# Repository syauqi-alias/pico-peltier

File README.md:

# pico-peltier
A TEC Controller using Pico RP2350 with Analog Devices LT8722 full bridge driver rated at 15V 4A

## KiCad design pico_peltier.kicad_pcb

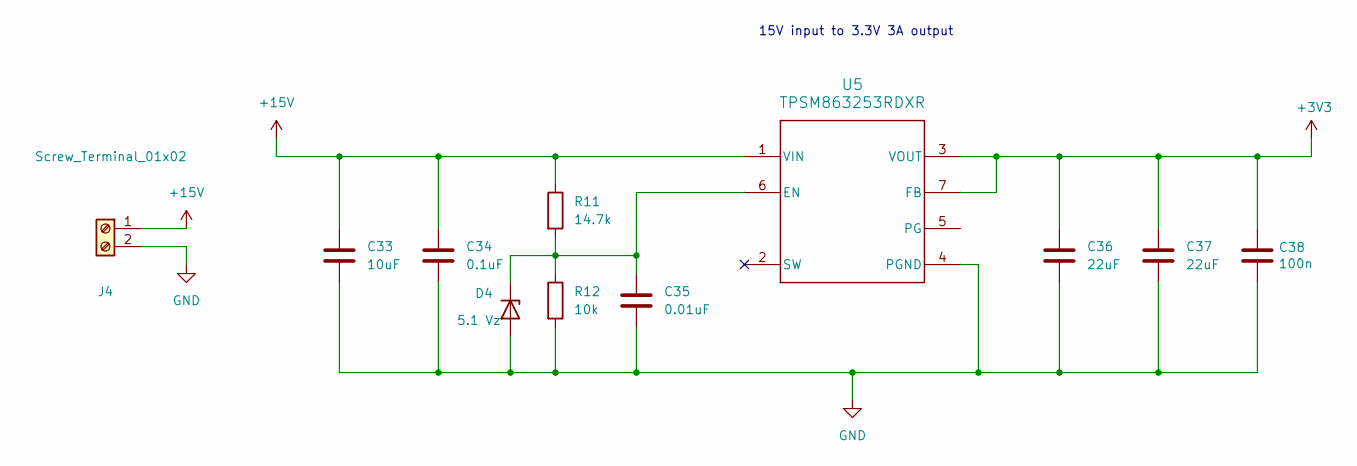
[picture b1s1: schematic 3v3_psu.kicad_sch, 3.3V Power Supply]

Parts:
C33: 10uF; C_0805_2012Metric_Pad1.18x1.45mm_HandSolder; mouser 187-CL21A106KAYNNNE
C34: 0.1uF; C_0805_2012Metric_Pad1.18x1.45mm_HandSolder; mouser 581-08053D104KAT2A
C35: 0.01uF; C_0805_2012Metric_Pad1.18x1.45mm_HandSolder; mouser KGM21NR71E103KT
C36, C37: 22uF; C_0603_1608Metric_Pad1.08x0.95mm_HandSolder; mouser 581-KAM15CT70J226KT
C38: 100n; C_0603_1608Metric_Pad1.08x0.95mm_HandSolder; mouser 581-KGM15AR70J104KM
D4: 5.1 Vz; D_SOD-123; mouser 621-MMSZ5231B-F
J4: Screw_Terminal_01x02; Altech_AK100_1x02_P5.00mm; mouser 845-30.002
R11: 14.7k; R_0603_1608Metric_Pad0.98x0.95mm_HandSolder; mouser 603-RC0603FR-1014K7L
R12: 10k; R_0603_1608Metric_Pad0.98x0.95mm_HandSolder; mouser 71-CRCW060310K0FKEE
U5: TPSM863253RDXR; VREG_TPSM863253RDXR; mouser 595-TPSM863253RDXR

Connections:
+3V3: C36.1, C37.1, C38.1, U5.3 (VOUT), U5.7 (FB), U5.14 (VOUT), U5.15 (VOUT), U5.16 (VOUT), U5.17 (VOUT), U5.18 (VOUT), U5.19 (VOUT); also elsewhere on the board
+15V: C33.1, C34.1, J4.1, R11.1, U5.1 (VIN); also elsewhere on the board
GND: C33.2, C34.2, C35.2, C36.2, C37.2, C38.2, D4.2 (A), J4.2, R12.2, U5.4 (PGND); also elsewhere on the board
unnamed: C35.1, D4.1 (K), R11.2, R12.1, U5.6 (EN)

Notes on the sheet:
15V input to 3.3V 3A output

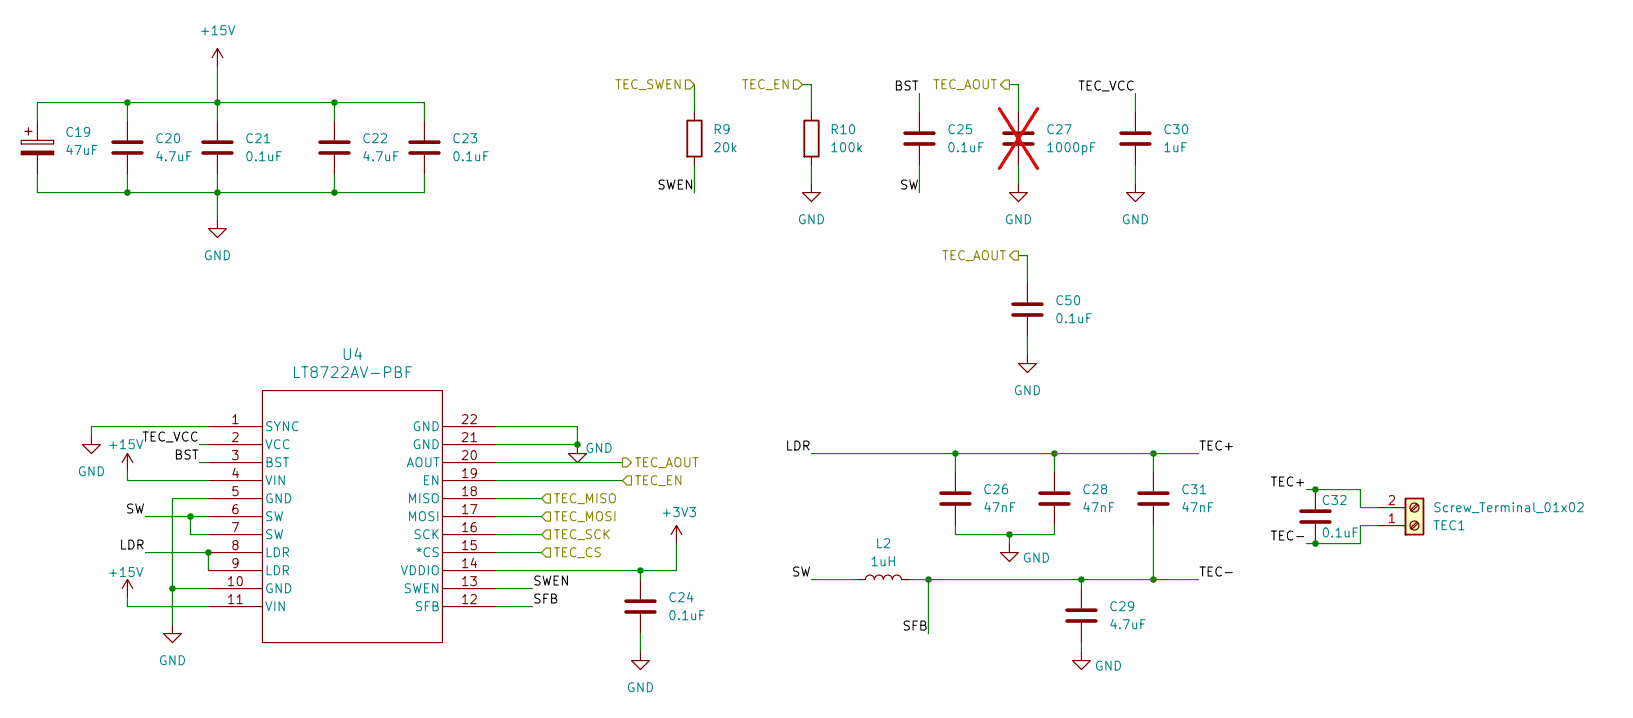
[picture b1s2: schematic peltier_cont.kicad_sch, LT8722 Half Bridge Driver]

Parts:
C19: 47uF; CP_EIA-7343-31_Kemet-D_HandSolder; mouser 581-TAJD476M020R
C20, C22, C29: 4.7uF; C_1206_3216Metric_Pad1.33x1.80mm_HandSolder; mouser 581-12063C475KAT2A
C21, C23, C24, C25, C32, C50: 0.1uF; C_0603_1608Metric_Pad1.08x0.95mm_HandSolder; mouser 187-CL10A104KA8NNNC
C26, C28, C31: 47nF; C_0603_1608Metric_Pad1.08x0.95mm_HandSolder; mouser 81-GCJ188R71E473KA1D
C27: 1000pF; C_0603_1608Metric_Pad1.08x0.95mm_HandSolder; mouser 581-06033C102KAT2A; not fitted
C30: 1uF; C_0603_1608Metric_Pad1.08x0.95mm_HandSolder; mouser 81-GCM188R71E105KA4D
L2: 1uH; L_Coilcraft_XAL4020-XXX; mouser 994-XAL4020-102MEC
R9: 20k; R_0603_1608Metric_Pad0.98x0.95mm_HandSolder; mouser 71-CRCW0603-20K-E3
R10: 100k; R_0603_1608Metric_Pad0.98x0.95mm_HandSolder; mouser 660-SG73P1JTTD1003F
TEC1: Screw_Terminal_01x02; Altech_AK100_1x02_P5.00mm; mouser 845-30.002
U4: LT8722AV-PBF; LQFN18_3X3X0.95_ADI-M; mouser 584-LT8722AVPBF

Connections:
+3V3: C24.1, U4.14 (VDDIO); also elsewhere on the board
+15V: C19.1, C20.1, C21.1, C22.1, C23.1, U4.4 (VIN), U4.11 (VIN); also elsewhere on the board
/mcu_rp2354a/GPIO20: U4.18 (MISO); also elsewhere on the board
/mcu_rp2354a/GPIO21: U4.16 (SCK); also elsewhere on the board
/mcu_rp2354a/GPIO22: U4.15 (*CS); also elsewhere on the board
/mcu_rp2354a/GPIO23: U4.17 (MOSI); also elsewhere on the board
/mcu_rp2354a/GPIO24: R9.1; also elsewhere on the board
/mcu_rp2354a/GPIO25: R10.1, U4.19 (EN); also elsewhere on the board
/mcu_rp2354a/GPIO29_ADC3: C27.1, C50.1, U4.20 (AOUT); also elsewhere on the board
/peltier_cont/BST: C25.1, U4.3 (BST)
/peltier_cont/LDR: C26.1, C28.1, C31.1, C32.1, TEC1.2, U4.8 (LDR), U4.9 (LDR)
/peltier_cont/SFB: C29.1, C31.2, C32.2, L2.2, TEC1.1, U4.12 (SFB)
/peltier_cont/SW: C25.2, L2.1, U4.6 (SW), U4.7 (SW)
/peltier_cont/SWEN: R9.2, U4.13 (SWEN)
/peltier_cont/TEC_VCC: C30.1, U4.2 (VCC)
GND: C19.2, C20.2, C21.2, C22.2, C23.2, C24.2, C26.2, C27.2, C28.2, C29.2, C30.2, C50.2, R10.2, U4.1 (SYNC), U4.5 (GND), U4.10 (GND), U4.21 (GND), U4.22 (GND); also elsewhere on the board

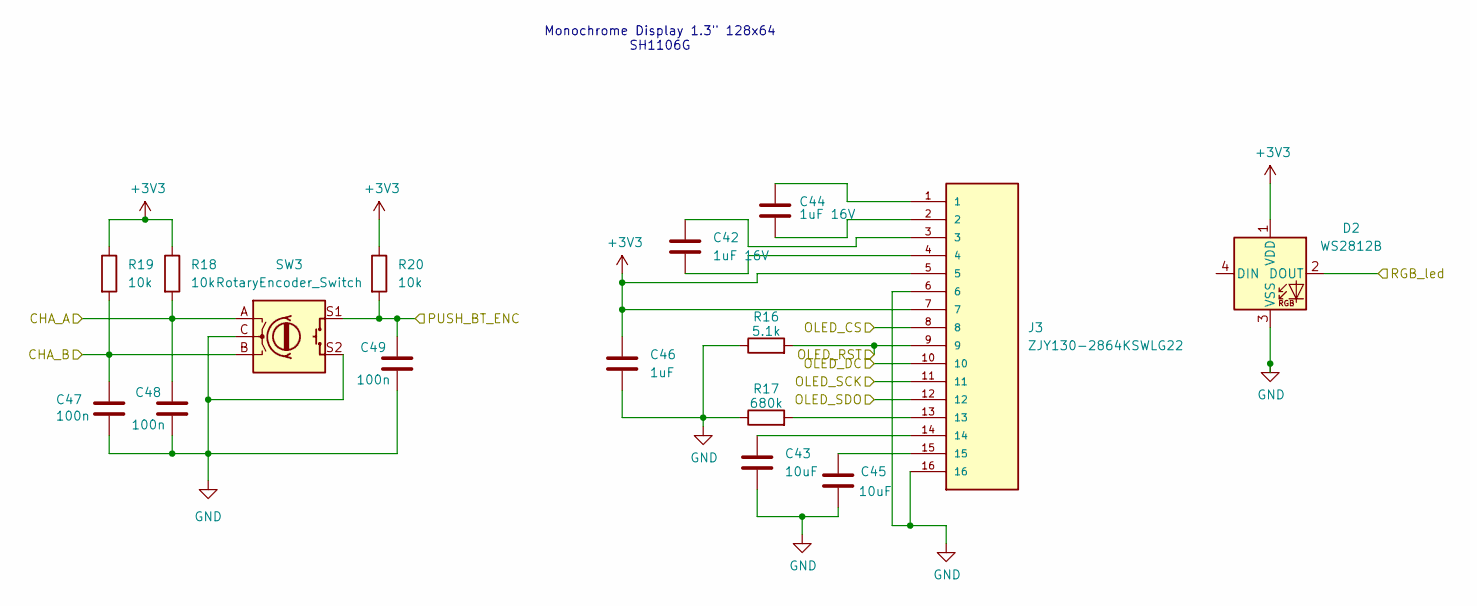
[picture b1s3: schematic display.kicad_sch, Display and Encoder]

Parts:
C42, C44: 1uF 16V; C_0603_1608Metric_Pad1.08x0.95mm_HandSolder; mouser 81-GCM188R71E105KA4D
C43, C45: 10uF; C_0805_2012Metric; mouser 187-CL21A106KAYNNNE
C46: 1uF; C_0603_1608Metric_Pad1.08x0.95mm_HandSolder; mouser 81-GCM188R71E105KA4D
C47, C48, C49: 100n; C_0603_1608Metric_Pad1.08x0.95mm_HandSolder; mouser 581-KGM15AR70J104KM
D2: WS2812B; LED_WS2812B_PLCC4_5.0x5.0mm_P3.2mm; mouser 474-COM-24837
J3: ZJY130-2864KSWLG22; AMPHENOL_F3311A7H121016E200; MPN F3311A7H121016E200; mouser 649-311A7H121016E200
R16: 5.1k; R_0603_1608Metric_Pad0.98x0.95mm_HandSolder; MPN CR0603-FX-5101ELF; mouser 652-CR0603FX-5101ELF
R17: 680k; R_0603_1608Metric_Pad0.98x0.95mm_HandSolder; MPN CRCW0603680KFKEAHP; mouser 71-CRCW0603680KFKEAH
R18, R19, R20: 10k; R_0603_1608Metric_Pad0.98x0.95mm_HandSolder; mouser 71-CRCW060310K0FKEE
SW3: RotaryEncoder_Switch; RotaryEncoder_Bourns_Vertical_PEC12R-3x17F-Sxxxx; mouser 652-PEC12R3220FS0024

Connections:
+3V3: C46.1, D2.1 (VDD), J3.5, J3.7, R18.1, R19.1, R20.1; also elsewhere on the board
/display/CHA_A: C48.1, R18.2, SW3.A; also elsewhere on the board
/display/CHA_B: C47.1, R19.2, SW3.B; also elsewhere on the board
/display/OLED_CS: J3.8; also elsewhere on the board
/display/OLED_DC: J3.10; also elsewhere on the board
/display/OLED_RST: J3.9, R16.2; also elsewhere on the board
/display/OLED_SCK: J3.11; also elsewhere on the board
/display/OLED_SDO: J3.12; also elsewhere on the board
/display/PUSH_BT_ENC: C49.1, R20.2, SW3.S1; also elsewhere on the board
/display/RGB_led: D2.2 (DOUT); also elsewhere on the board
GND: C43.2, C45.2, C46.2, C47.2, C48.2, C49.2, D2.3 (VSS), J3.6, J3.16, R16.1, R17.1, SW3.C, SW3.S2; also elsewhere on the board
unnamed: C42.1, J3.3
unnamed: C42.2, J3.4
unnamed: C43.1, J3.14
unnamed: C44.1, J3.1
unnamed: C44.2, J3.2
unnamed: C45.1, J3.15
unnamed: J3.13, R17.2

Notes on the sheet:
Monochrome Display 1.3" 128x64 SH1106G

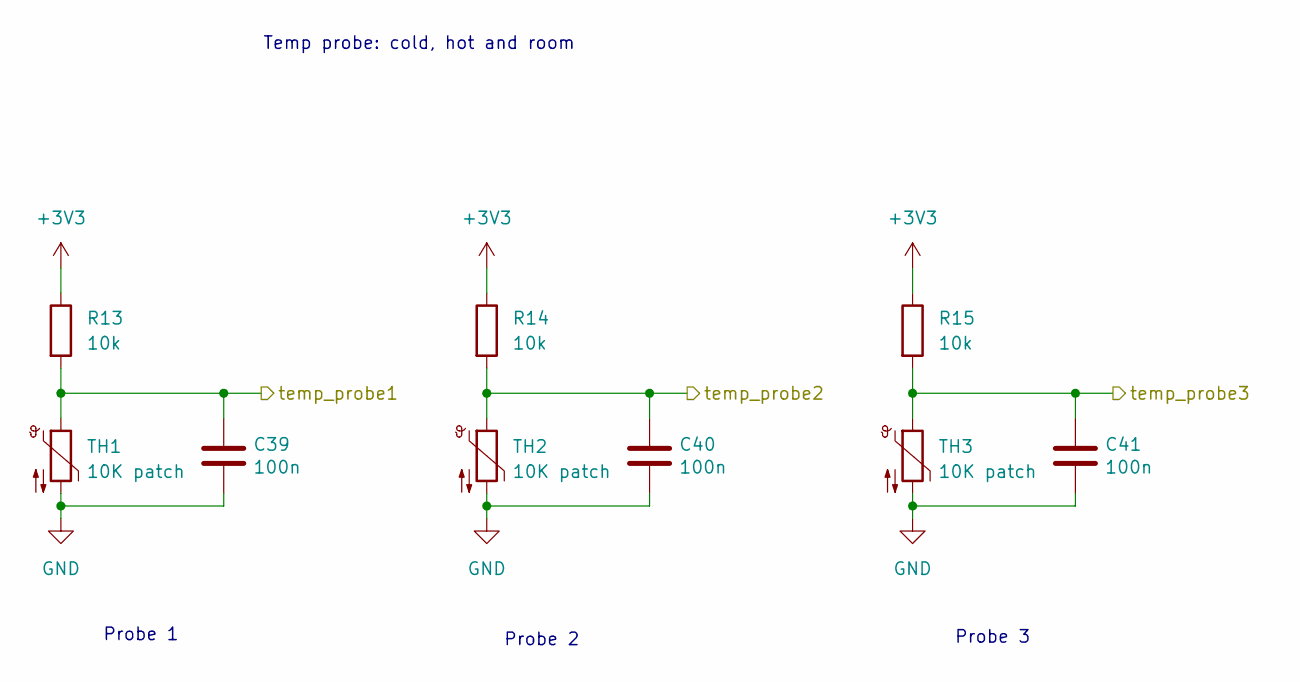
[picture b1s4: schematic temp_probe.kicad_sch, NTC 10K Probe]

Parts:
C39, C40, C41: 100n; C_0603_1608Metric_Pad1.08x0.95mm_HandSolder; mouser 581-KGM15AR70J104KM
R13, R14, R15: 10k; R_0603_1608Metric_Pad0.98x0.95mm_HandSolder; mouser 603-RT0603WRE0710KL
TH1, TH2, TH3: 10K patch; Altech_AK100_1x02_P5.00mm; mouser 845-30.002

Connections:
+3V3: R13.1, R14.1, R15.1; also elsewhere on the board
/mcu_rp2354a/GPIO26_ADC0: C39.1, R13.2, TH1.1; also elsewhere on the board
/mcu_rp2354a/GPIO27_ADC1: C40.1, R14.2, TH2.1; also elsewhere on the board
/mcu_rp2354a/GPIO28_ADC2: C41.1, R15.2, TH3.1; also elsewhere on the board
GND: C39.2, C40.2, C41.2, TH1.2, TH2.2, TH3.2; also elsewhere on the board

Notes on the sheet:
Temp probe: cold, hot and room
Probe 1
Probe 2
Probe 3

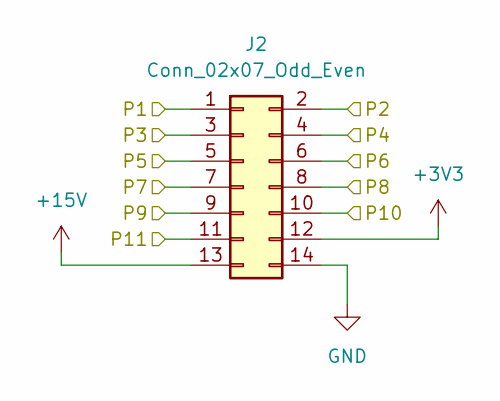
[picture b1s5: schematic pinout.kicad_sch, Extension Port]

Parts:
J2: Conn_02x07_Odd_Even; PinSocket_2x07_P2.54mm_Vertical; mouser 571-5-534236-7

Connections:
+3V3: J2.12; also elsewhere on the board
+15V: J2.13; also elsewhere on the board
/mcu_rp2354a/GPIO0: J2.1; also elsewhere on the board
/mcu_rp2354a/GPIO1: J2.2; also elsewhere on the board
/mcu_rp2354a/GPIO2: J2.3; also elsewhere on the board
/mcu_rp2354a/GPIO12: J2.4; also elsewhere on the board
/mcu_rp2354a/GPIO13: J2.5; also elsewhere on the board
/mcu_rp2354a/GPIO14: J2.6; also elsewhere on the board
/mcu_rp2354a/GPIO15: J2.7; also elsewhere on the board
/mcu_rp2354a/GPIO16: J2.8; also elsewhere on the board
/mcu_rp2354a/GPIO17: J2.9; also elsewhere on the board
/mcu_rp2354a/GPIO18: J2.10; also elsewhere on the board
/mcu_rp2354a/GPIO19: J2.11; also elsewhere on the board
GND: J2.14; also elsewhere on the board

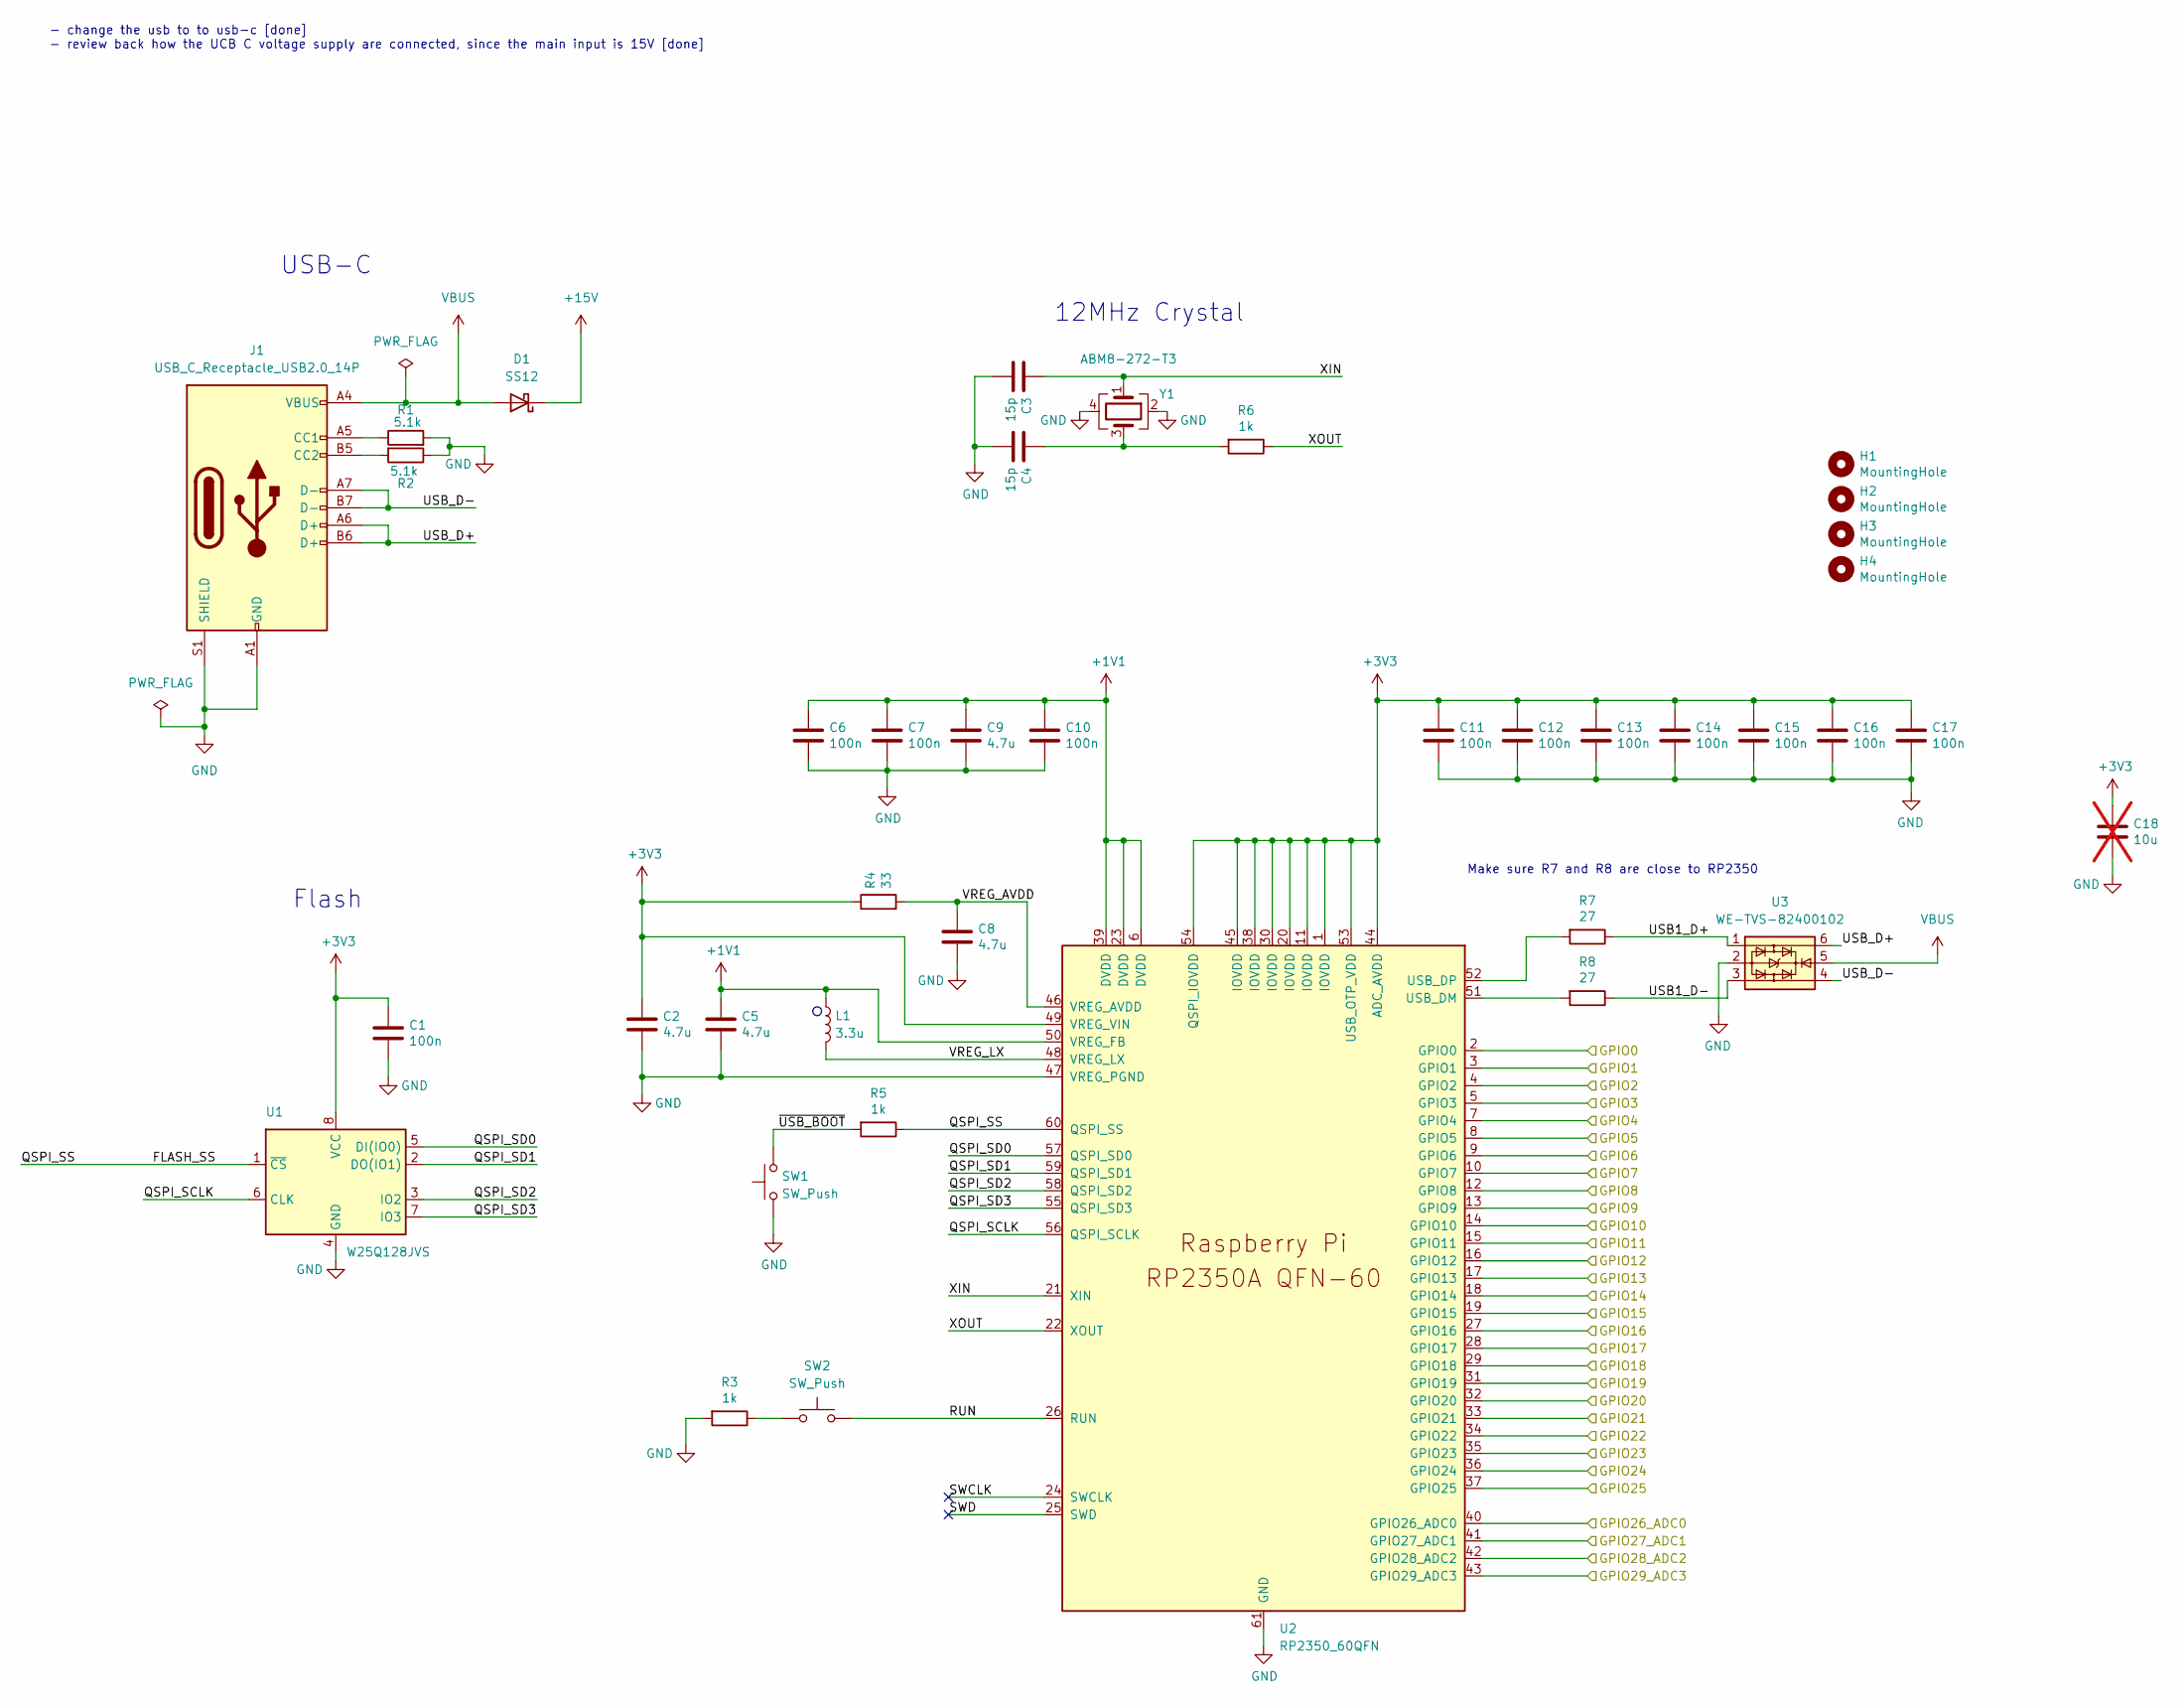
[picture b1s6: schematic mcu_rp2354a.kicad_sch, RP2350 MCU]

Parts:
C1, C6, C7, C10, C11, C12, C13, C14, C15, C16, C17: 100n; C_0603_1608Metric_Pad1.08x0.95mm_HandSolder; mouser 581-KGM15AR70J104KM
C2, C5, C8, C9: 4.7u; C_0603_1608Metric_Pad1.08x0.95mm_HandSolder; mouser 81-GRM188Z71A475KE5D
C3, C4: 15p; C_0603_1608Metric_Pad1.08x0.95mm_HandSolder; mouser 603-CC603FRNPO9BN150
C18: 10u; C_0805_2012Metric; not fitted
D1: SS12; D_SMA; MPN SS12; mouser 625-SS12-E3
H1, H2, H3, H4: MountingHole; MountingHole_2.7mm_M2.5_DIN965_Pad_TopBottom
J1: USB_C_Receptacle_USB2.0_14P; USB_C_Receptacle_JAE_DX07S016JA1R1500; LCSC TYPE-C-31-M-12
L1: 3.3u; L_pol_2016; mouser 815-AB201610S3R3101T
R1, R2: 5.1k; R_0603_1608Metric_Pad0.98x0.95mm_HandSolder; MPN CR0603-FX-5101ELF; mouser 652-CR0603FX-5101ELF
R3, R5, R6: 1k; R_0603_1608Metric_Pad0.98x0.95mm_HandSolder; mouser 603-RC0603FR-101KL
R4: 33; R_0603_1608Metric_Pad0.98x0.95mm_HandSolder; mouser 279-CRGCQ0603F33R
R7, R8: 27; R_0603_1608Metric_Pad0.98x0.95mm_HandSolder; mouser 603-RC0603FR-1327RL
SW1, SW2: SW_Push; SW_Push_1P1T_NO_Vertical_Wuerth_434133025816; MPN 434133025816; mouser 710-434133025816
U1: W25Q128JVS; SOIC-8_5.3x5.3mm_P1.27mm; MPN W25Q128JVSIM TR; mouser 454-W25Q128JVSIMTR
U2: RP2350_60QFN; RP2350-QFN-60-1EP_7x7_P0.4mm_EP3.4x3.4mm_ThermalVias; mouser 358-SC1509
U3: WE-TVS-82400102; SOT-23-6; MPN 82400102; mouser 710-82400102
Y1: ABM8-272-T3; Crystal_SMD_3225-4Pin_3.2x2.5mm; Farnell 4331750

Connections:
+1V1: C5.1, C6.1, C7.1, C9.1, C10.1, L1.1, U2.6 (DVDD), U2.23 (DVDD), U2.39 (DVDD), U2.50 (VREG_FB)
+3V3: C1.1, C2.1, C11.1, C12.1, C13.1, C14.1, C15.1, C16.1, C17.1, C18.1, R4.1, U1.8 (VCC), U2.1 (IOVDD), U2.11 (IOVDD), U2.20 (IOVDD), U2.30 (IOVDD), U2.38 (IOVDD), U2.44 (ADC_AVDD), U2.45 (IOVDD), U2.49 (VREG_VIN), U2.53 (USB_OTP_VDD), U2.54 (QSPI_IOVDD); also elsewhere on the board
+15V: D1.1 (K); also elsewhere on the board
/display/CHA_A: U2.7 (GPIO4); also elsewhere on the board
/display/CHA_B: U2.8 (GPIO5); also elsewhere on the board
/display/OLED_CS: U2.13 (GPIO9); also elsewhere on the board
/display/OLED_DC: U2.10 (GPIO7); also elsewhere on the board
/display/OLED_RST: U2.12 (GPIO8); also elsewhere on the board
/display/OLED_SCK: U2.14 (GPIO10); also elsewhere on the board
/display/OLED_SDO: U2.15 (GPIO11); also elsewhere on the board
/display/PUSH_BT_ENC: U2.9 (GPIO6); also elsewhere on the board
/display/RGB_led: U2.5 (GPIO3); also elsewhere on the board
/mcu_rp2354a/FLASH_SS: R5.1, U1.1 (~CS), U2.60 (QSPI_SS)
/mcu_rp2354a/GPIO0: U2.2 (GPIO0); also elsewhere on the board
/mcu_rp2354a/GPIO1: U2.3 (GPIO1); also elsewhere on the board
/mcu_rp2354a/GPIO2: U2.4 (GPIO2); also elsewhere on the board
/mcu_rp2354a/GPIO12: U2.16 (GPIO12); also elsewhere on the board
/mcu_rp2354a/GPIO13: U2.17 (GPIO13); also elsewhere on the board
/mcu_rp2354a/GPIO14: U2.18 (GPIO14); also elsewhere on the board
/mcu_rp2354a/GPIO15: U2.19 (GPIO15); also elsewhere on the board
/mcu_rp2354a/GPIO16: U2.27 (GPIO16); also elsewhere on the board
/mcu_rp2354a/GPIO17: U2.28 (GPIO17); also elsewhere on the board
/mcu_rp2354a/GPIO18: U2.29 (GPIO18); also elsewhere on the board
/mcu_rp2354a/GPIO19: U2.31 (GPIO19); also elsewhere on the board
/mcu_rp2354a/GPIO20: U2.32 (GPIO20); also elsewhere on the board
/mcu_rp2354a/GPIO21: U2.33 (GPIO21); also elsewhere on the board
/mcu_rp2354a/GPIO22: U2.34 (GPIO22); also elsewhere on the board
/mcu_rp2354a/GPIO23: U2.35 (GPIO23); also elsewhere on the board
/mcu_rp2354a/GPIO24: U2.36 (GPIO24); also elsewhere on the board
/mcu_rp2354a/GPIO25: U2.37 (GPIO25); also elsewhere on the board
/mcu_rp2354a/GPIO26_ADC0: U2.40 (GPIO26_ADC0); also elsewhere on the board
/mcu_rp2354a/GPIO27_ADC1: U2.41 (GPIO27_ADC1); also elsewhere on the board
/mcu_rp2354a/GPIO28_ADC2: U2.42 (GPIO28_ADC2); also elsewhere on the board
/mcu_rp2354a/GPIO29_ADC3: U2.43 (GPIO29_ADC3); also elsewhere on the board
/mcu_rp2354a/QSPI_SCLK: U1.6 (CLK), U2.56 (QSPI_SCLK)
/mcu_rp2354a/QSPI_SD0: U1.5 (DI(IO0)), U2.57 (QSPI_SD0)
/mcu_rp2354a/QSPI_SD1: U1.2 (DO(IO1)), U2.59 (QSPI_SD1)
/mcu_rp2354a/QSPI_SD2: U1.3 (IO2), U2.58 (QSPI_SD2)
/mcu_rp2354a/QSPI_SD3: U1.7 (IO3), U2.55 (QSPI_SD3)
/mcu_rp2354a/RUN: SW2.2, U2.26 (RUN)
/mcu_rp2354a/SWCLK: U2.24 (SWCLK)
/mcu_rp2354a/SWD: U2.25 (SWD)
/mcu_rp2354a/USB1_D+: R7.1, U3.1
/mcu_rp2354a/USB1_D-: R8.1, U3.3
/mcu_rp2354a/USB_D+: J1.A6 (D+), J1.B6 (D+), U3.6
/mcu_rp2354a/USB_D-: J1.A7 (D-), J1.B7 (D-), U3.4
/mcu_rp2354a/VREG_AVDD: C8.1, R4.2, U2.46 (VREG_AVDD)
/mcu_rp2354a/VREG_LX: L1.2, U2.48 (VREG_LX)
/mcu_rp2354a/XIN: C3.1, U2.21 (XIN), Y1.1
/mcu_rp2354a/XOUT: R6.1, U2.22 (XOUT)
/mcu_rp2354a/~USB_BOOT: R5.2, SW1.2
GND: C1.2, C2.2, C3.2, C4.2, C5.2, C6.2, C7.2, C8.2, C9.2, C10.2, C11.2, C12.2, C13.2, C14.2, C15.2, C16.2, C17.2, C18.2, H1.1, H2.1, H3.1, H4.1, J1.A1 (GND), J1.A12 (GND), J1.B1 (GND), J1.B12 (GND), J1.S1 (SHIELD), R1.2, R2.1, R3.2, SW1.1, U1.4 (GND), U2.47 (VREG_PGND), U2.61 (GND), U3.2, Y1.2, Y1.4; also elsewhere on the board
unnamed: C4.1, R6.2, Y1.3
unnamed: J1.A5 (CC1), R1.1
unnamed: J1.B5 (CC2), R2.2
unnamed: R3.1, SW2.1
unnamed: R8.2, U2.51 (USB_DM)
unnamed: R7.2, U2.52 (USB_DP)
VBUS: D1.2 (A), J1.A4 (VBUS), J1.A9 (VBUS), J1.B4 (VBUS), J1.B9 (VBUS), U3.5

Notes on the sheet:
12MHz Crystal
USB-C
- change the usb to to usb-c [done] - review back how the UCB C voltage supply are connected, since the main input is 15V [done]
Flash
Make sure R7 and R8 are close to RP2350

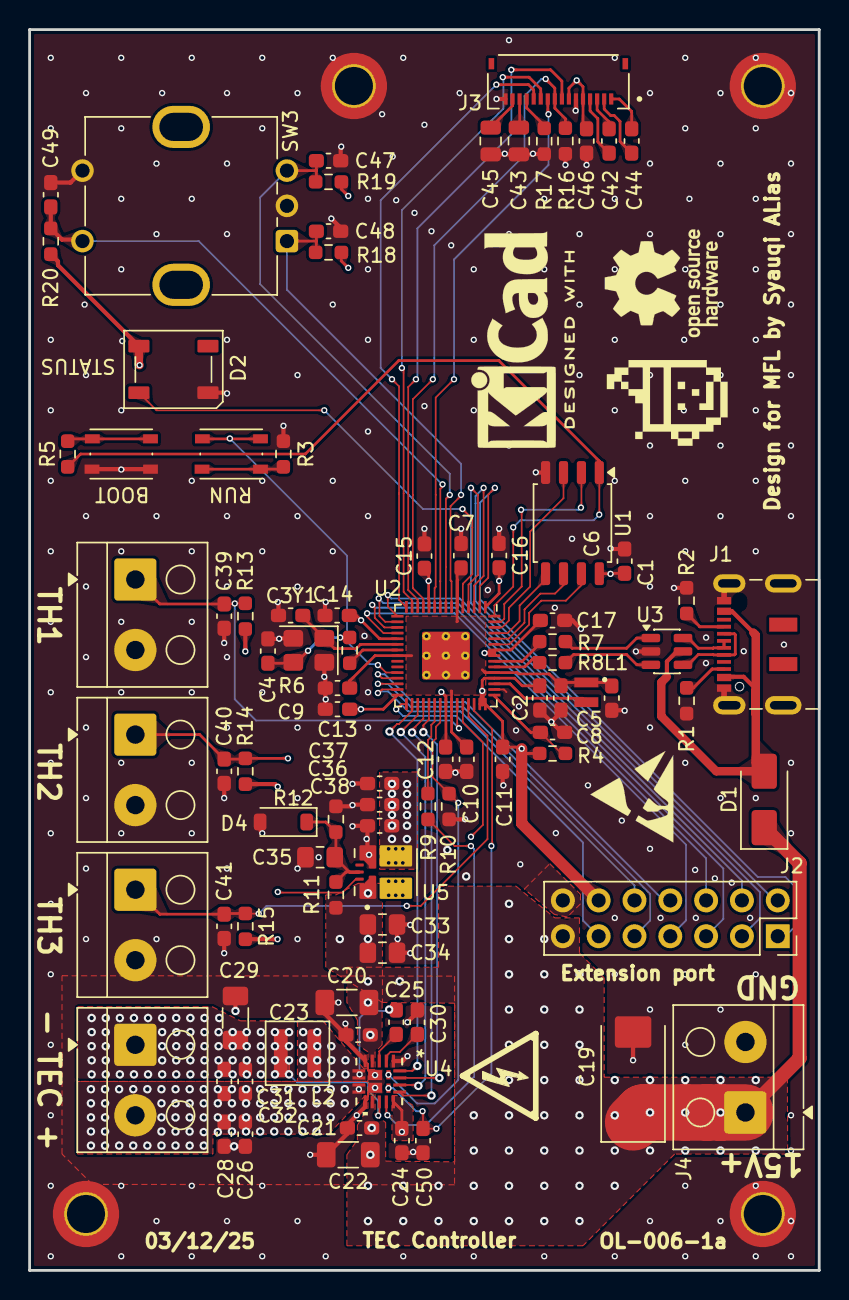
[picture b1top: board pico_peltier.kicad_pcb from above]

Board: 4 copper layers, 56.0 x 88.0 mm, 94 parts (0 on the bottom side), 71 nets.

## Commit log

2025-12-04 entire project
2025-12-04 sch PDF
2025-12-04 finalising
2025-12-04 finalising again
2025-12-10 update all
2025-12-11 final update before fab
2025-12-11 picture
2025-12-11 Add image to README for prototype visualization
2025-12-16 fix silkscreen
